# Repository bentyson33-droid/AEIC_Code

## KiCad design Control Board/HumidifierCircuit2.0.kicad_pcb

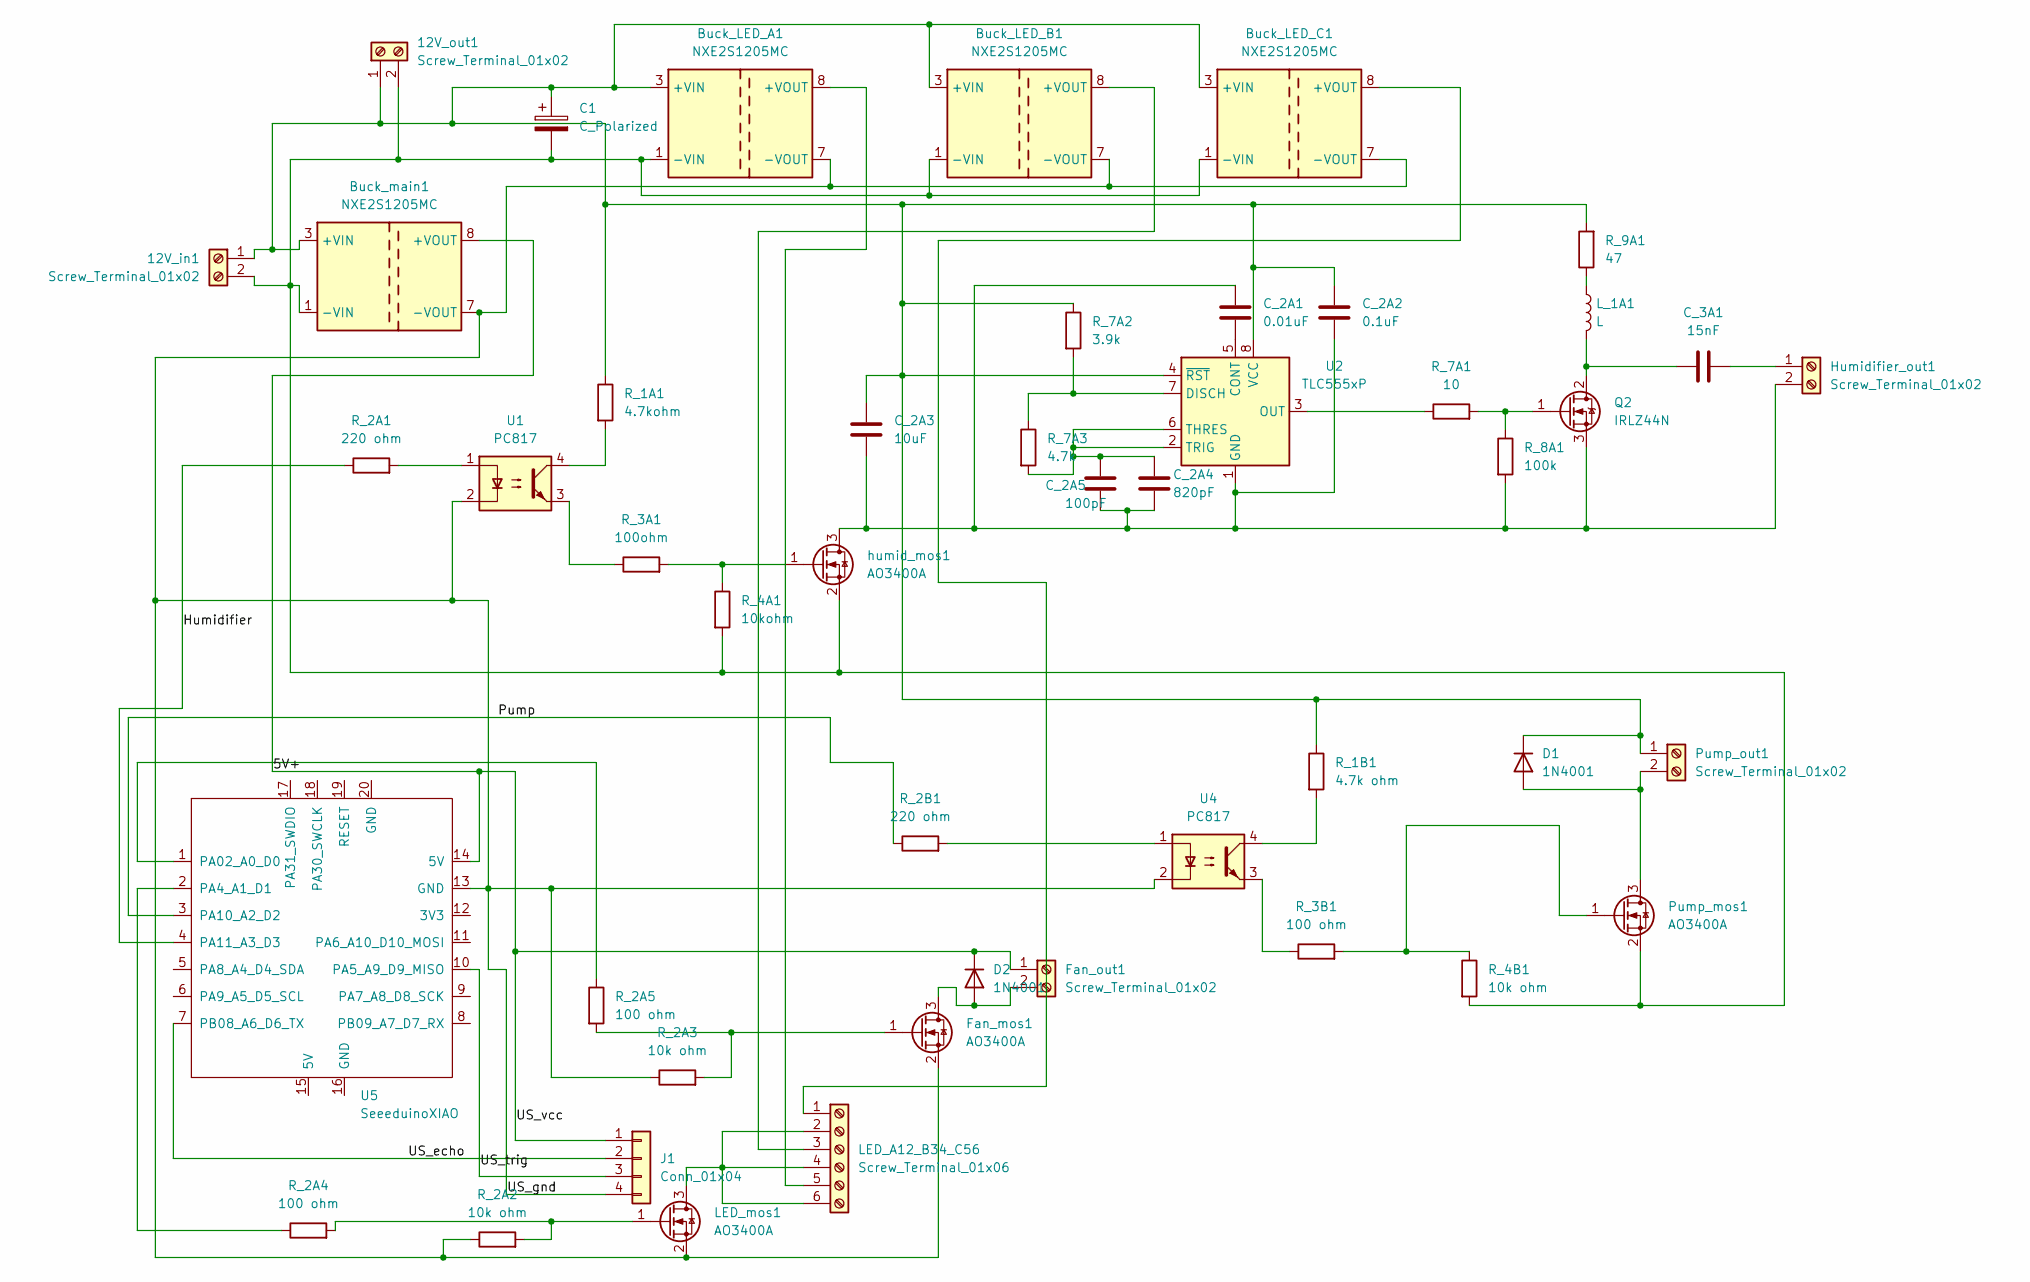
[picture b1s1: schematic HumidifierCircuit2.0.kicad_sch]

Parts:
12V_in1, 12V_out1: Screw_Terminal_01x02; TerminalBlock_Phoenix_MKDS-1,5-2-5.08_1x02_P5.08mm_Horizont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
Buck_LED_A1: NXE2S1205MC; Converter_DCDC_Murata_NXExSxxxxMC_SMD
Buck_LED_B1: NXE2S1205MC; Converter_DCDC_Murata_NXExSxxxxMC_SMD
Buck_LED_C1: NXE2S1205MC; Converter_DCDC_Murata_NXExSxxxxMC_SMD
Buck_main1: NXE2S1205MC; Converter_DCDC_Murata_NXExSxxxxMC_SMD
C1: C_Polarized; CP_Radial_D13.0mm_P5.00mm
C_2A1: 0.01uF; C_Axial_L3.8mm_D2.6mm_P7.50mm_Horizontal
C_2A2: 0.1uF; C_Axial_L12.0mm_D6.5mm_P15.00mm_Horizontal
C_2A3: 10uF; C_Axial_L3.8mm_D2.6mm_P7.50mm_Horizontal
C_2A4: 820pF; C_Axial_L3.8mm_D2.6mm_P7.50mm_Horizontal
C_2A5: 100pF; C_Axial_L3.8mm_D2.6mm_P7.50mm_Horizontal
C_3A1: 15nF; C_Rect_L7.0mm_W2.0mm_P5.00mm
D1, D2: 1N4001; D_DO-41_SOD81_P10.16mm_Horizontal
Fan_mos1: AO3400A; SOT-23
Fan_out1: Screw_Terminal_01x02; TerminalBlock_Phoenix_MKDS-1,5-2-5.08_1x02_P5.08mm_Horizont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
Humidifier_out1: Screw_Terminal_01x02; TerminalBlock_Phoenix_MKDS-1,5-2-5.08_1x02_P5.08mm_Horizont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
J1: Conn_01x04; PinHeader_1x04_P2.54mm_Vertical
LED_A12_B34_C56: Screw_Terminal_01x06; TerminalBlock_Phoenix_MKDS-1,5-6-5.08_1x06_P5.08mm_Horizont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
LED_mos1: AO3400A; SOT-23
L_1A1: L; L_Axial_L9.5mm_D4.0mm_P5.08mm_Vertical_Fastron_SMCC
Pump_mos1: AO3400A; SOT-23
Pump_out1: Screw_Terminal_01x02; TerminalBlock_Phoenix_MKDS-1,5-2-5.08_1x02_P5.08mm_Horizont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
Q2: IRLZ44N; TO-220-3_Vertical
R_1A1: 4.7kohm; R_Axial_DIN0207_L6.3mm_D2.5mm_P7.62mm_Horizontal
R_1B1: 4.7k ohm; R_Axial_DIN0207_L6.3mm_D2.5mm_P7.62mm_Horizontal
R_2A1, R_2B1: 220 ohm; R_Axial_DIN0207_L6.3mm_D2.5mm_P7.62mm_Horizontal
R_2A2, R_2A3, R_4B1: 10k ohm; R_Axial_DIN0207_L6.3mm_D2.5mm_P7.62mm_Horizontal
R_2A4, R_2A5, R_3B1: 100 ohm; R_Axial_DIN0207_L6.3mm_D2.5mm_P7.62mm_Horizontal
R_3A1: 100ohm; R_Axial_DIN0207_L6.3mm_D2.5mm_P7.62mm_Horizontal
R_4A1: 10kohm; R_Axial_DIN0207_L6.3mm_D2.5mm_P7.62mm_Horizontal
R_7A1: 10; R_Axial_DIN0207_L6.3mm_D2.5mm_P7.62mm_Horizontal
R_7A2: 3.9k; R_Axial_DIN0207_L6.3mm_D2.5mm_P7.62mm_Horizontal
R_7A3: 4.7k; R_Axial_DIN0207_L6.3mm_D2.5mm_P7.62mm_Horizontal
R_8A1: 100k; R_Axial_DIN0207_L6.3mm_D2.5mm_P7.62mm_Horizontal
R_9A1: 47; R_Axial_DIN0207_L6.3mm_D2.5mm_P7.62mm_Horizontal
U1, U4: PC817; SOIC254P1016X460-4N
U2: TLC555xP; DIP-8_W7.62mm
U5: SeeeduinoXIAO; XIAO-ESP32-C3-SMD
humid_mos1: AO3400A; SOT-23

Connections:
/5V+: Buck_main1.8 (+VOUT), D2.1 (K), Fan_out1.1, J1.1, U5.14 (5V)
/Humidifier: R_2A1.1, U5.4 (PA11_A3_D3)
/Pump: R_2B1.1, U5.3 (PA10_A2_D2)
/US_echo: J1.2, U5.7 (PB08_A6_D6_TX)
/US_gnd: Buck_LED_A1.7 (-VOUT), Buck_LED_B1.7 (-VOUT), Buck_LED_C1.7 (-VOUT), Buck_main1.7 (-VOUT), Fan_mos1.2 (S), J1.4, LED_mos1.2 (S), R_2A2.1, R_2A3.1, U1.2, U4.2, U5.13 (GND)
/US_trig: J1.3, U5.10 (PA5_A9_D9_MISO)
unnamed: 12V_in1.1, 12V_out1.1, Buck_LED_A1.3 (+VIN), Buck_LED_B1.3 (+VIN), Buck_LED_C1.3 (+VIN), Buck_main1.3 (+VIN), C1.1, C_2A2.2, C_2A3.2, D1.1 (K), Pump_out1.1, R_1A1.1, R_1B1.1, R_7A2.1, R_9A1.2, U2.4 (~RST), U2.8 (VCC)
unnamed: 12V_in1.2, 12V_out1.2, Buck_LED_A1.1 (-VIN), Buck_LED_B1.1 (-VIN), Buck_LED_C1.1 (-VIN), Buck_main1.1 (-VIN), C1.2, Pump_mos1.2 (S), R_4A1.2, R_4B1.2, humid_mos1.2 (S)
unnamed: Buck_LED_A1.8 (+VOUT), LED_A12_B34_C56.5
unnamed: Buck_LED_B1.8 (+VOUT), LED_A12_B34_C56.3
unnamed: Buck_LED_C1.8 (+VOUT), LED_A12_B34_C56.1
unnamed: D1.2 (A), Pump_mos1.3 (D), Pump_out1.2
unnamed: D2.2 (A), Fan_mos1.3 (D), Fan_out1.2
unnamed: Fan_mos1.1 (G), R_2A3.2, R_2A5.2
unnamed: C_3A1.2, Humidifier_out1.1
unnamed: C_2A1.2, C_2A2.1, C_2A3.1, C_2A4.1, C_2A5.1, Humidifier_out1.2, Q2.3 (S), R_8A1.2, U2.1 (GND), humid_mos1.3 (D)
unnamed: LED_A12_B34_C56.2, LED_A12_B34_C56.4, LED_A12_B34_C56.6, LED_mos1.3 (D)
unnamed: LED_mos1.1 (G), R_2A2.2, R_2A4.2
unnamed: L_1A1.1, R_9A1.1
unnamed: Pump_mos1.1 (G), R_3B1.2, R_4B1.1
unnamed: C_3A1.1, L_1A1.2, Q2.2 (D)
unnamed: Q2.1 (G), R_7A1.2, R_8A1.1
unnamed: R_1A1.2, U1.4
unnamed: R_1B1.2, U4.4
unnamed: R_2A1.2, U1.1
unnamed: R_2B1.2, U4.1
unnamed: R_3A1.1, U1.3
unnamed: R_3B1.1, U4.3
unnamed: C_2A1.1, U2.5 (CONT)
unnamed: R_7A2.2, R_7A3.1, U2.7 (DISCH)
unnamed: R_7A1.1, U2.3 (OUT)
unnamed: C_2A4.2, C_2A5.2, R_7A3.2, U2.2 (TRIG), U2.6 (THRES)
unnamed: R_2A5.1, U5.1 (PA02_A0_D0)
unnamed: R_2A4.1, U5.2 (PA4_A1_D1)
unnamed: R_3A1.2, R_4A1.1, humid_mos1.1 (G)

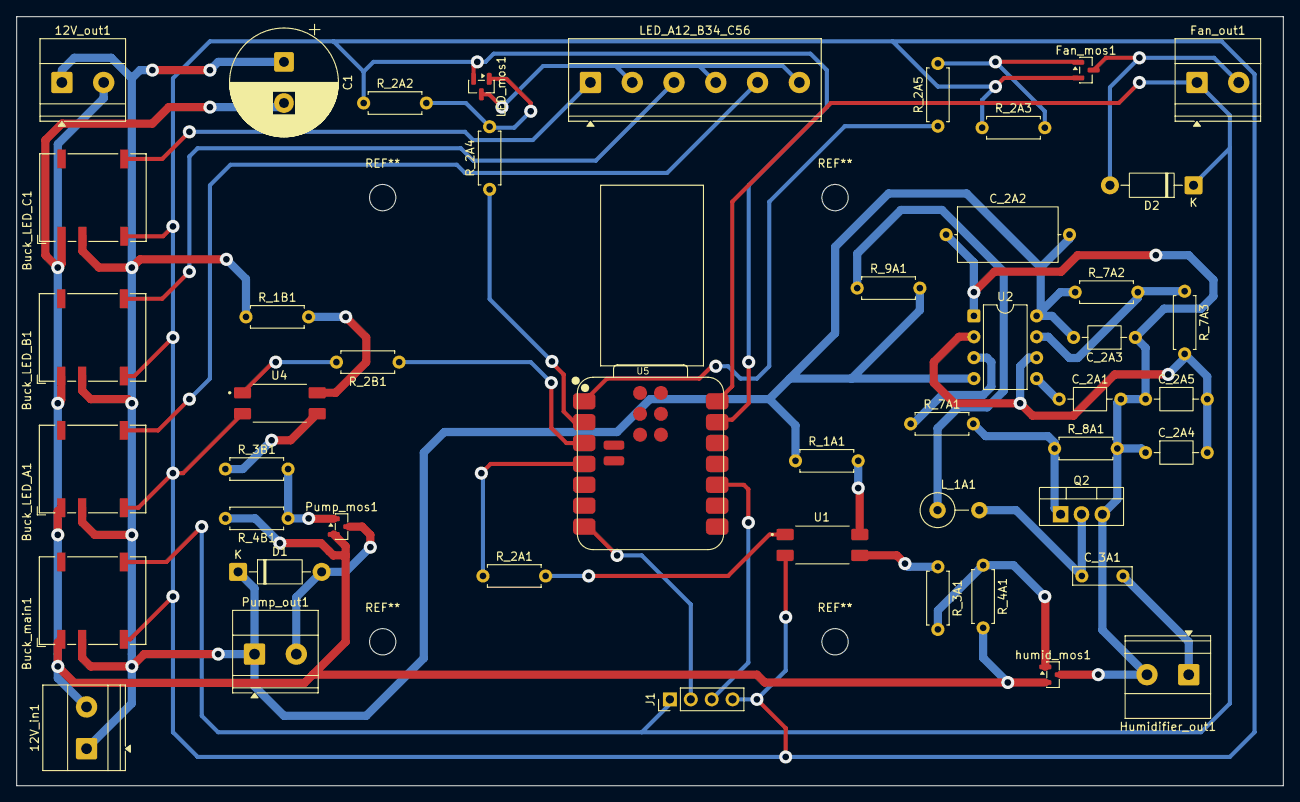
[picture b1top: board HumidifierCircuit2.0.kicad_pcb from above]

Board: 2 copper layers, 154.0 x 93.5 mm, 47 parts (0 on the bottom side), 35 nets.

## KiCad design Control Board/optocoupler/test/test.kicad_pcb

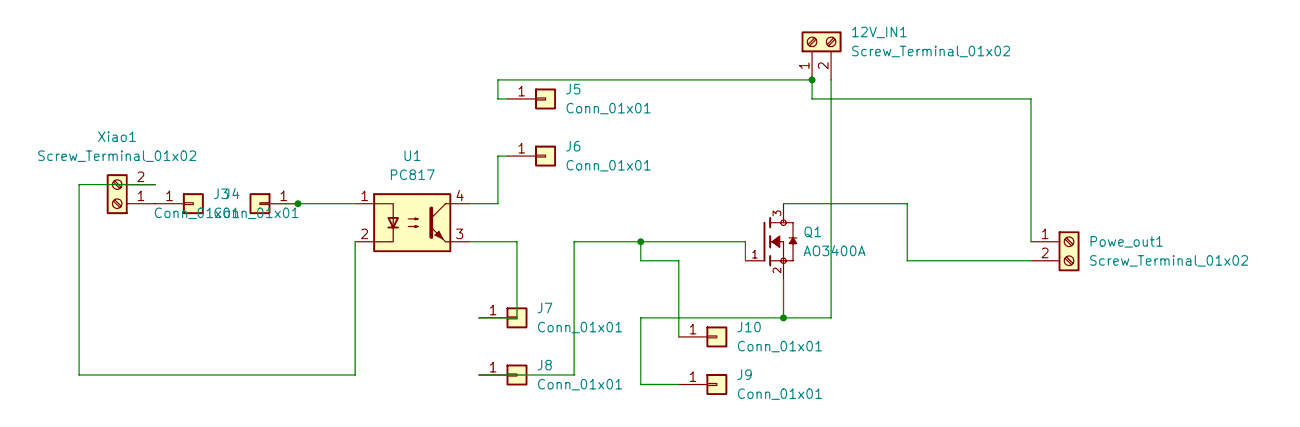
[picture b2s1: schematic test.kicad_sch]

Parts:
12V_IN1: Screw_Terminal_01x02; TerminalBlock_Phoenix_MKDS-1,5-2-5.08_1x02_P5.08mm_Horizont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
J3, J4, J5, J6, J7, J8, J9, J10: Conn_01x01; SolderWire-0.1sqmm_1x01_D0.4mm_OD1mm
Powe_out1: Screw_Terminal_01x02; TerminalBlock_Phoenix_MKDS-1,5-2-5.08_1x02_P5.08mm_Horizont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
Q1: AO3400A; SOT95P280X125-3N; PARTREV L
U1: PC817; SOIC254P1016X460-4N
Xiao1: Screw_Terminal_01x02; TerminalBlock_Phoenix_MKDS-1,5-2-5.08_1x02_P5.08mm_Horizont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

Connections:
unnamed: 12V_IN1.1, J5.1, Powe_out1.1
unnamed: 12V_IN1.2, J9.1, Q1.2
unnamed: J3.1, Xiao1.1
unnamed: J4.1, U1.1
unnamed: J6.1, U1.4
unnamed: J7.1, U1.3
unnamed: J8.1, J10.1, Q1.1
unnamed: Powe_out1.2, Q1.3
unnamed: U1.2, Xiao1.2

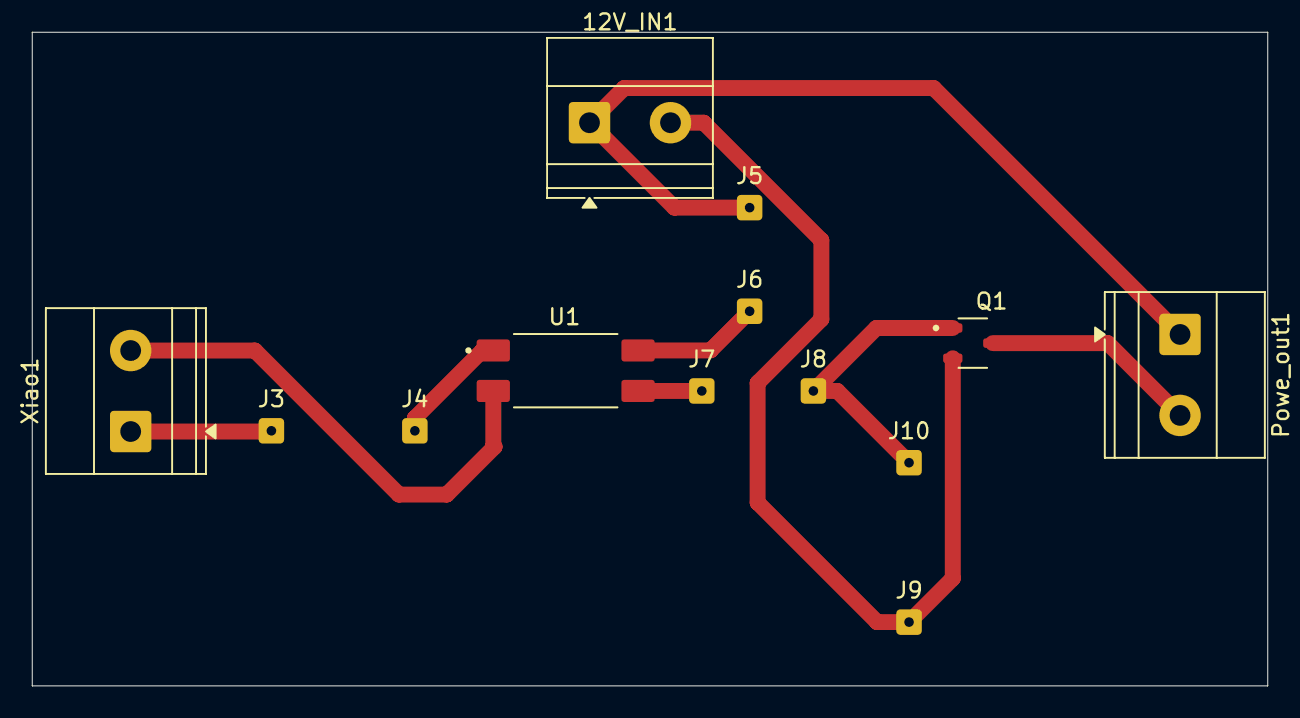
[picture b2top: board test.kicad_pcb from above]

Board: 2 copper layers, 77.5 x 41.0 mm, 13 parts (0 on the bottom side), 9 nets.

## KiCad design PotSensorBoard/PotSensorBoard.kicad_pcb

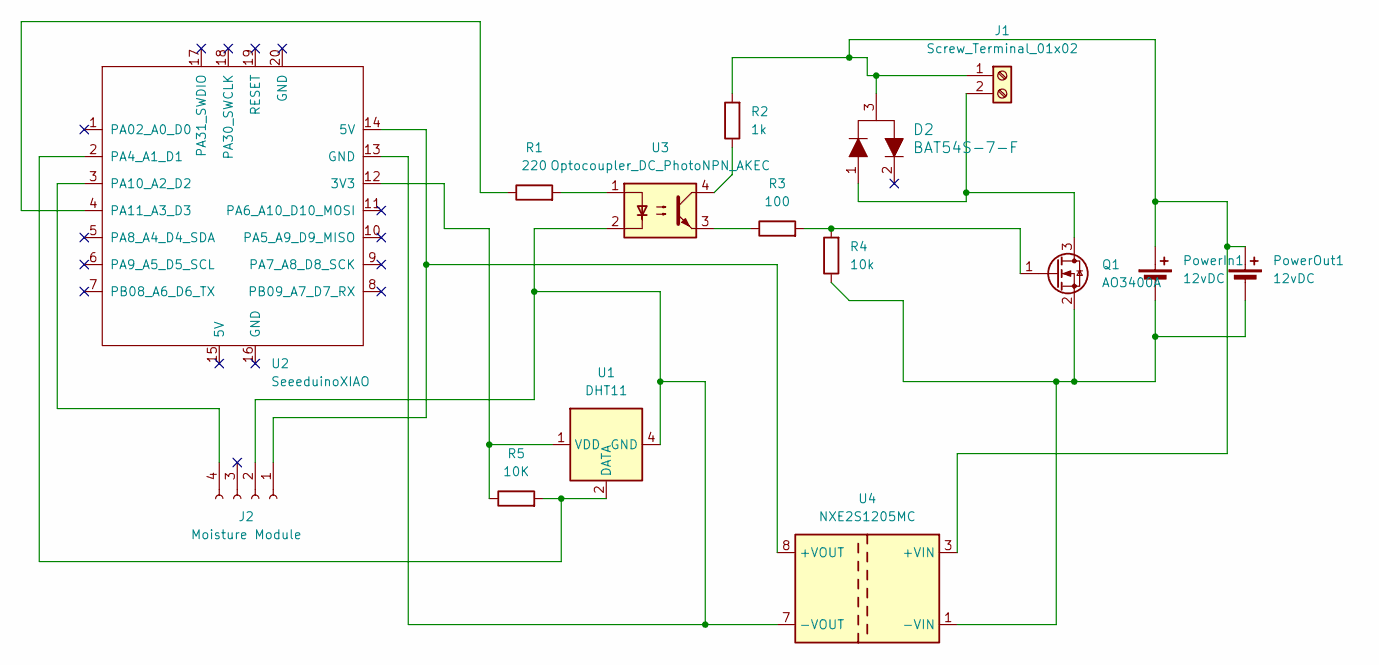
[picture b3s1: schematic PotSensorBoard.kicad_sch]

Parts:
D2: BAT54S-7-F; SOT-23; MPN BAT54S-7-F; Digi-Key_PN BAT54S-FDICT-ND
J1: Screw_Terminal_01x02; TerminalBlock_Phoenix_MKDS-1,5-2-5.08_1x02_P5.08mm_Horizont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
J2: Moisture Module; PinSocket_1x04_P2.54mm_Vertical
PowerIn1: 12vDC; TerminalBlock_Phoenix_MKDS-1,5-2-5.08_1x02_P5.08mm_Horizont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
PowerOut1: 12vDC; TerminalBlock_Phoenix_MKDS-1,5-2-5.08_1x02_P5.08mm_Horizont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
Q1: AO3400A; SOT-23
R1: 220; C_0805_2012Metric_Pad1.18x1.45mm_HandSolder
R2: 1k; C_0805_2012Metric_Pad1.18x1.45mm_HandSolder
R3: 100; R_1206_3216Metric_Pad1.30x1.75mm_HandSolder
R4: 10k; C_0805_2012Metric_Pad1.18x1.45mm_HandSolder
R5: 10K; C_0805_2012Metric_Pad1.18x1.45mm_HandSolder
U1: DHT11; Aosong_DHT11_5.5x12.0_P2.54mm
U2: SeeeduinoXIAO; MCU_Seeed_ESP32C3
U3: Optocoupler_DC_PhotoNPN_AKEC; SMDIP-4_W11.48mm
U4: NXE2S1205MC; Converter_DCDC_Murata_NXExSxxxxMC_SMD

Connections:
unnamed: D2.3, J1.1, PowerIn1.1 (+), PowerOut1.1 (+), R2.2, U4.3 (+VIN)
unnamed: D2.1, J1.2, Q1.3 (D)
unnamed: J2.1, U2.14 (5V), U4.8 (+VOUT)
unnamed: J2.2, U1.4 (GND), U2.13 (GND), U3.2, U4.7 (-VOUT)
unnamed: J2.4, U2.3 (PA10_A2_D2)
unnamed: PowerIn1.2 (-), PowerOut1.2 (-), Q1.2 (S), R4.1, U4.1 (-VIN)
unnamed: Q1.1 (G), R3.2, R4.2
unnamed: R1.2, U3.1
unnamed: R2.1, U3.4
unnamed: R3.1, U3.3
unnamed: R5.2, U1.2 (DATA), U2.2 (PA4_A1_D1)
unnamed: R5.1, U1.1 (VDD), U2.12 (3V3)
unnamed: R1.1, U2.4 (PA11_A3_D3)

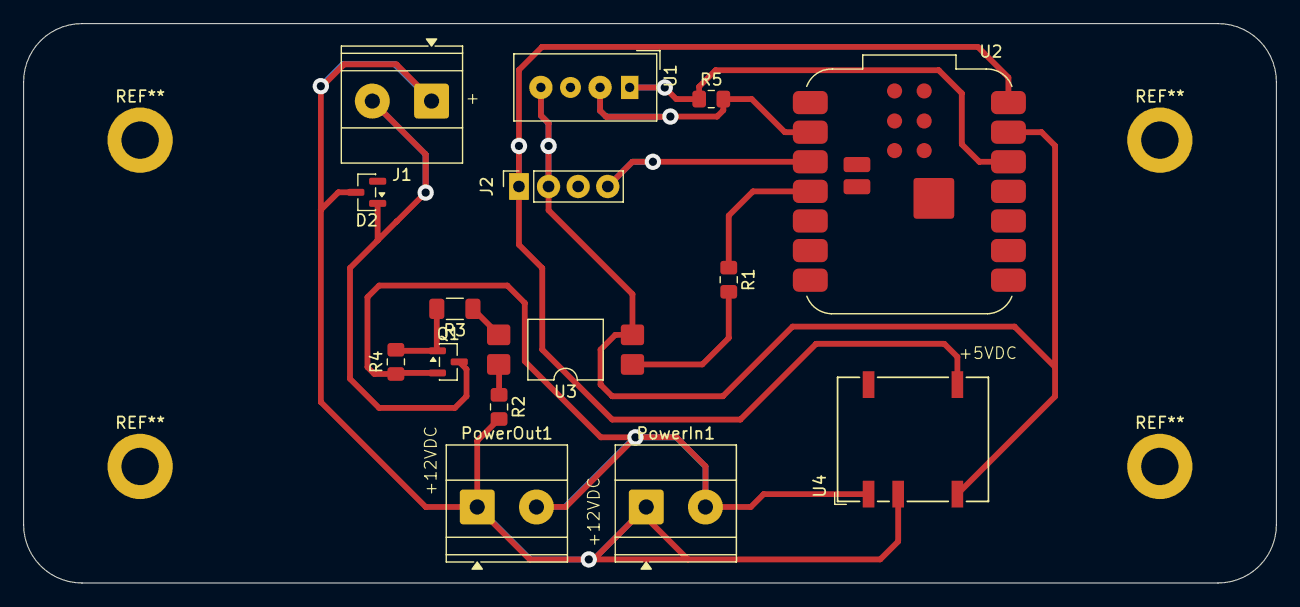
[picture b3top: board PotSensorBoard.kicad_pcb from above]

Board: 2 copper layers, 107.5 x 48.0 mm, 15 parts (0 on the bottom side), 13 nets.

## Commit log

2026-03-17 Create CYDupdates
2026-03-17 Create XIAOupdates
2026-03-17 Update CYDupdates
2026-03-17 Update XIAOupdates
2026-03-18 Create CYD_WIP
